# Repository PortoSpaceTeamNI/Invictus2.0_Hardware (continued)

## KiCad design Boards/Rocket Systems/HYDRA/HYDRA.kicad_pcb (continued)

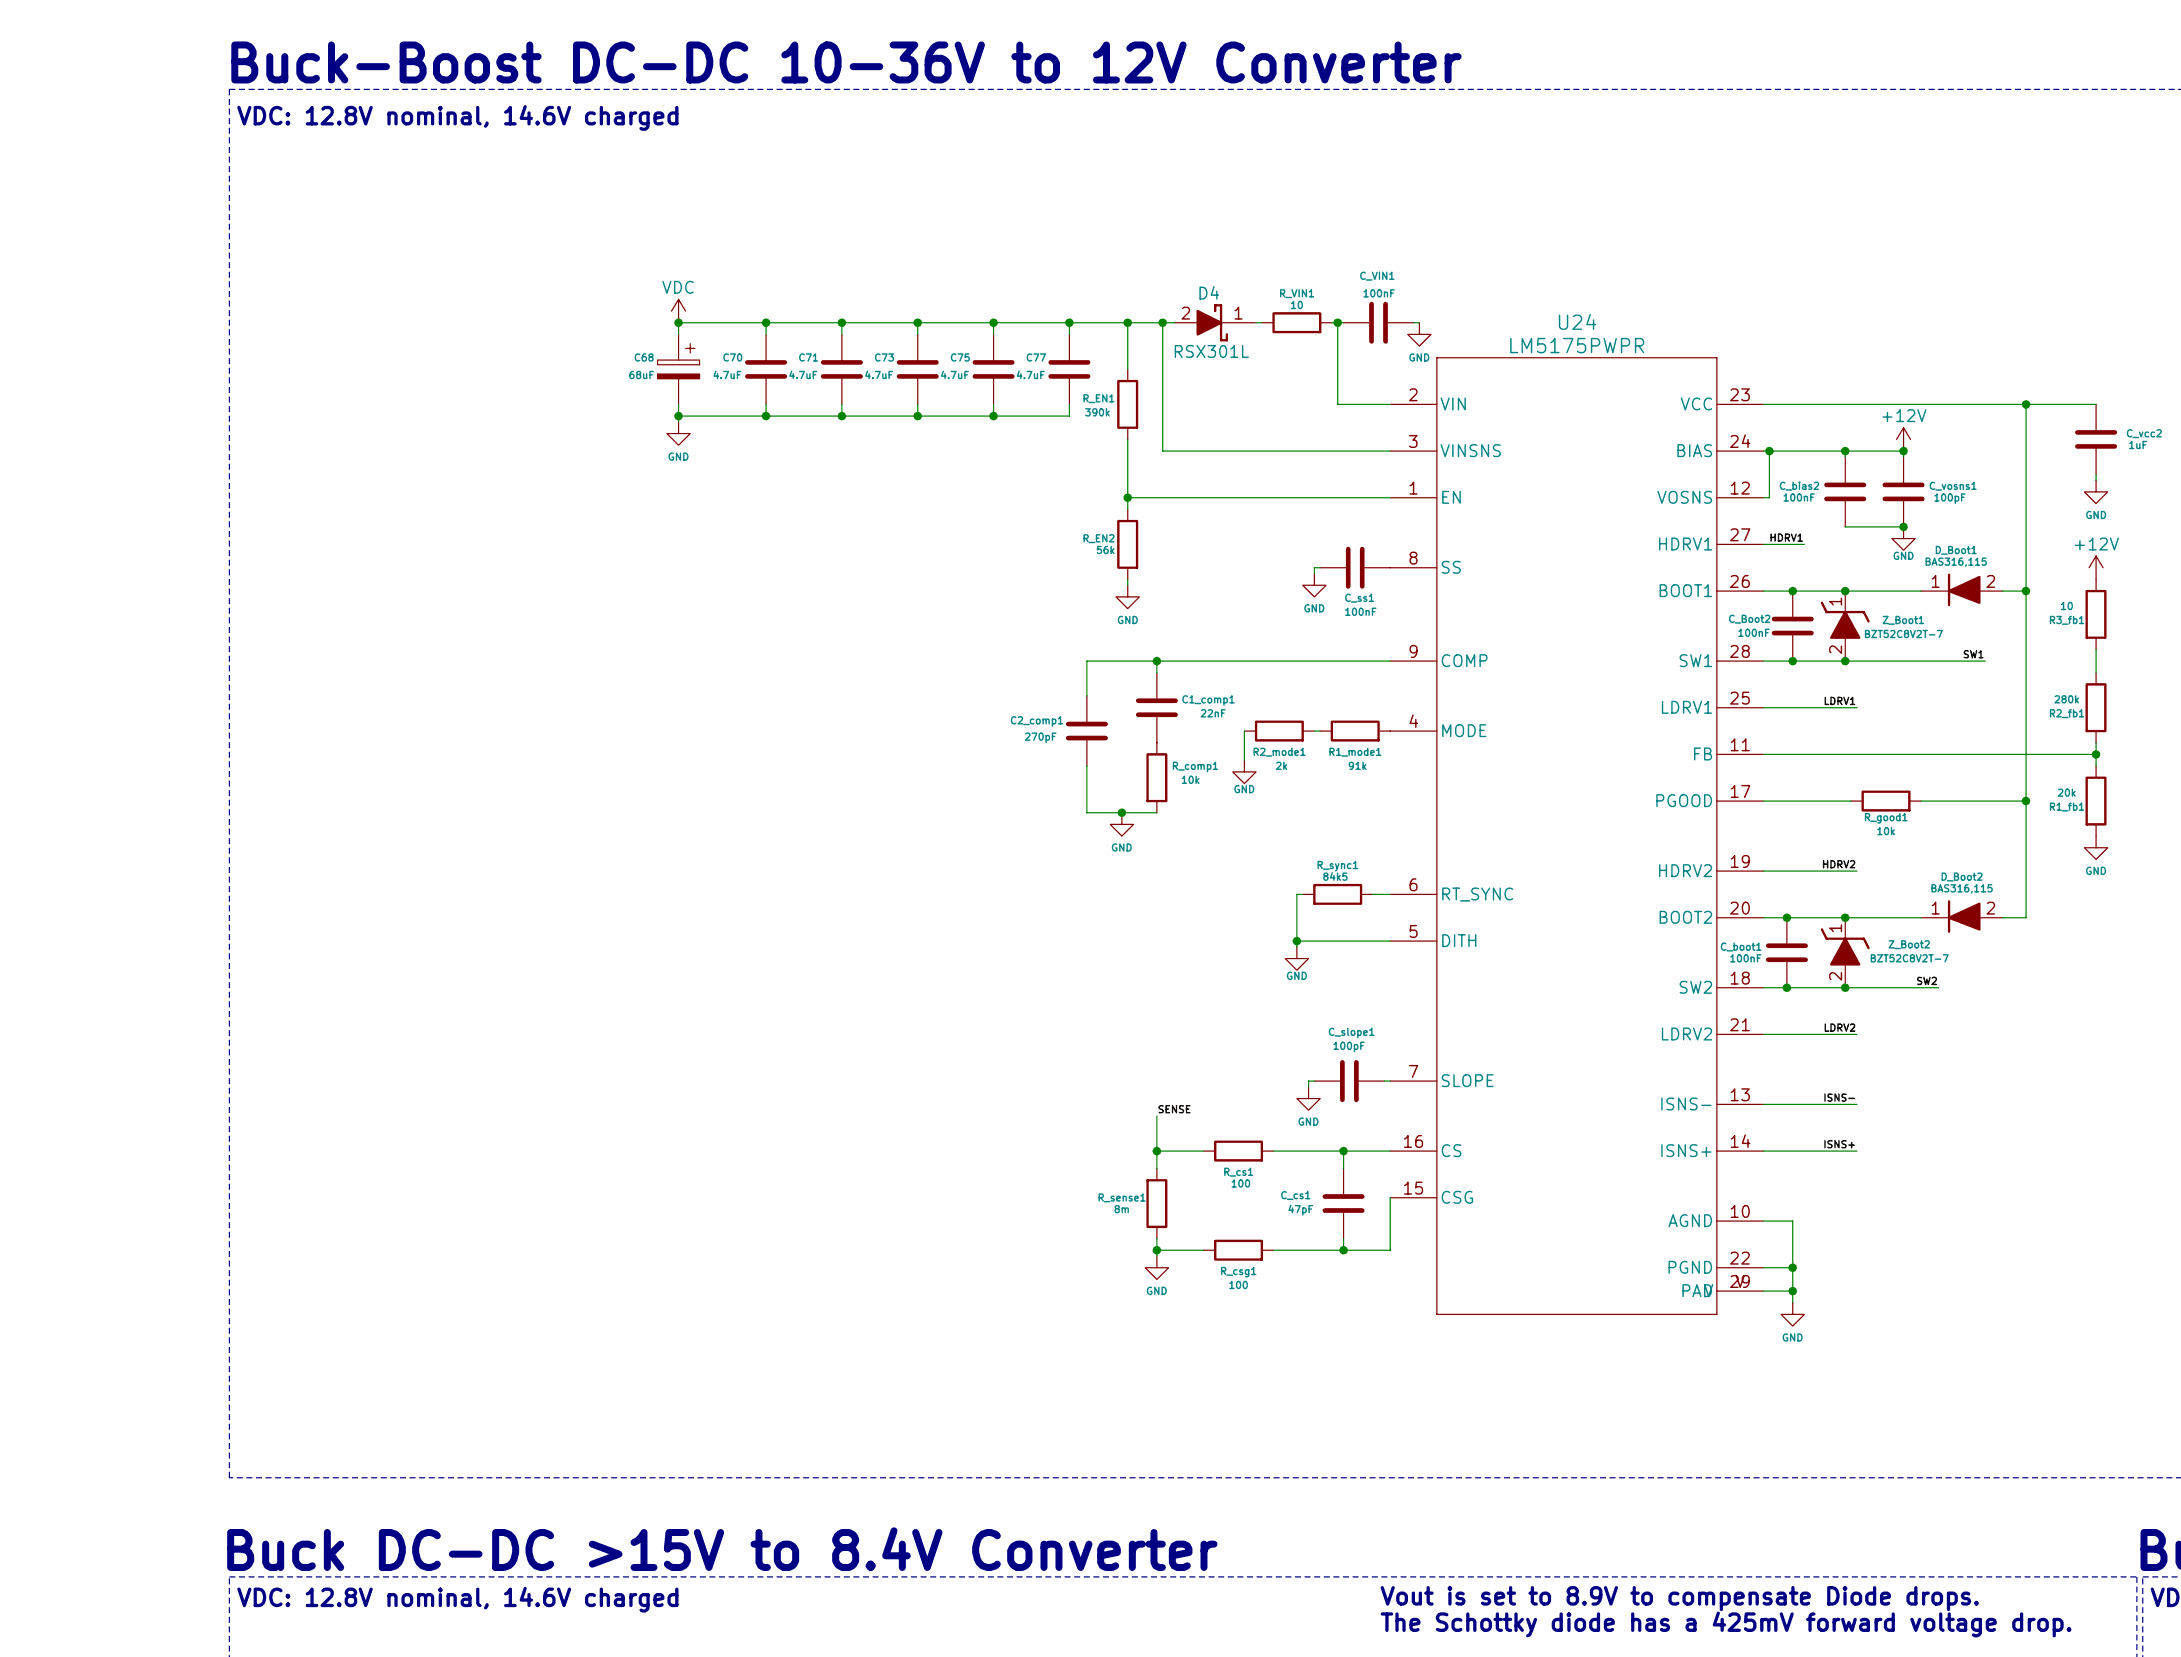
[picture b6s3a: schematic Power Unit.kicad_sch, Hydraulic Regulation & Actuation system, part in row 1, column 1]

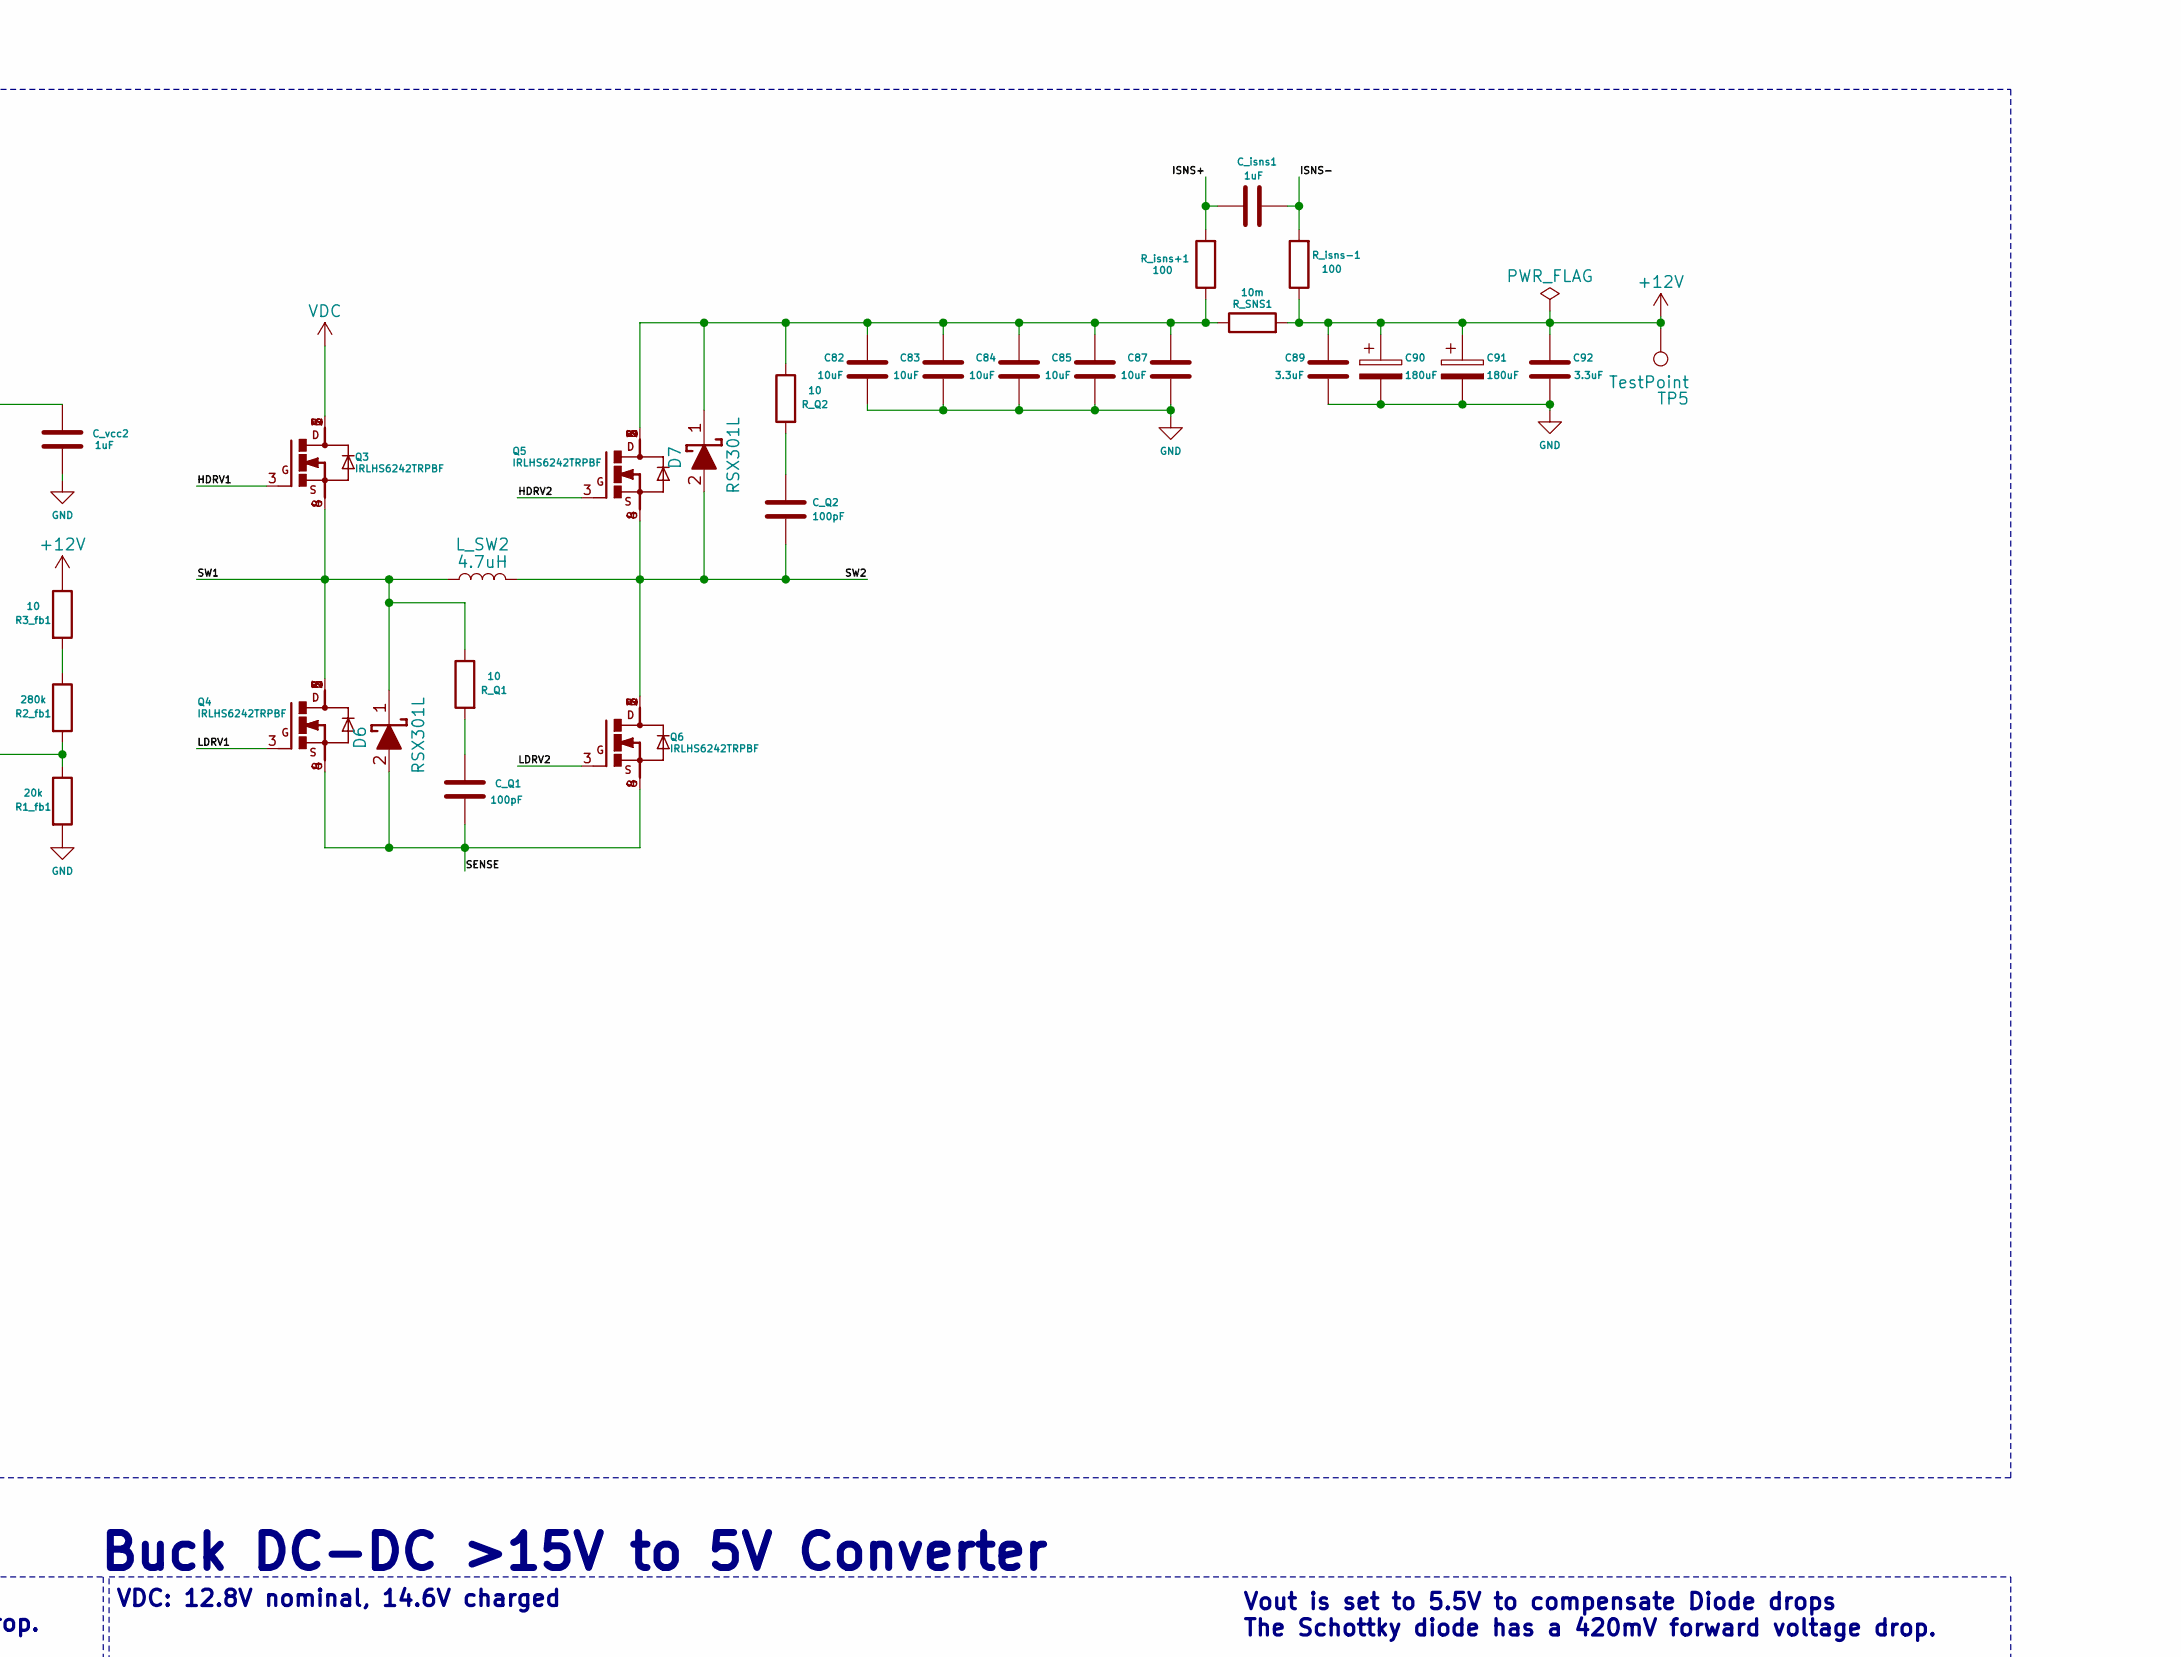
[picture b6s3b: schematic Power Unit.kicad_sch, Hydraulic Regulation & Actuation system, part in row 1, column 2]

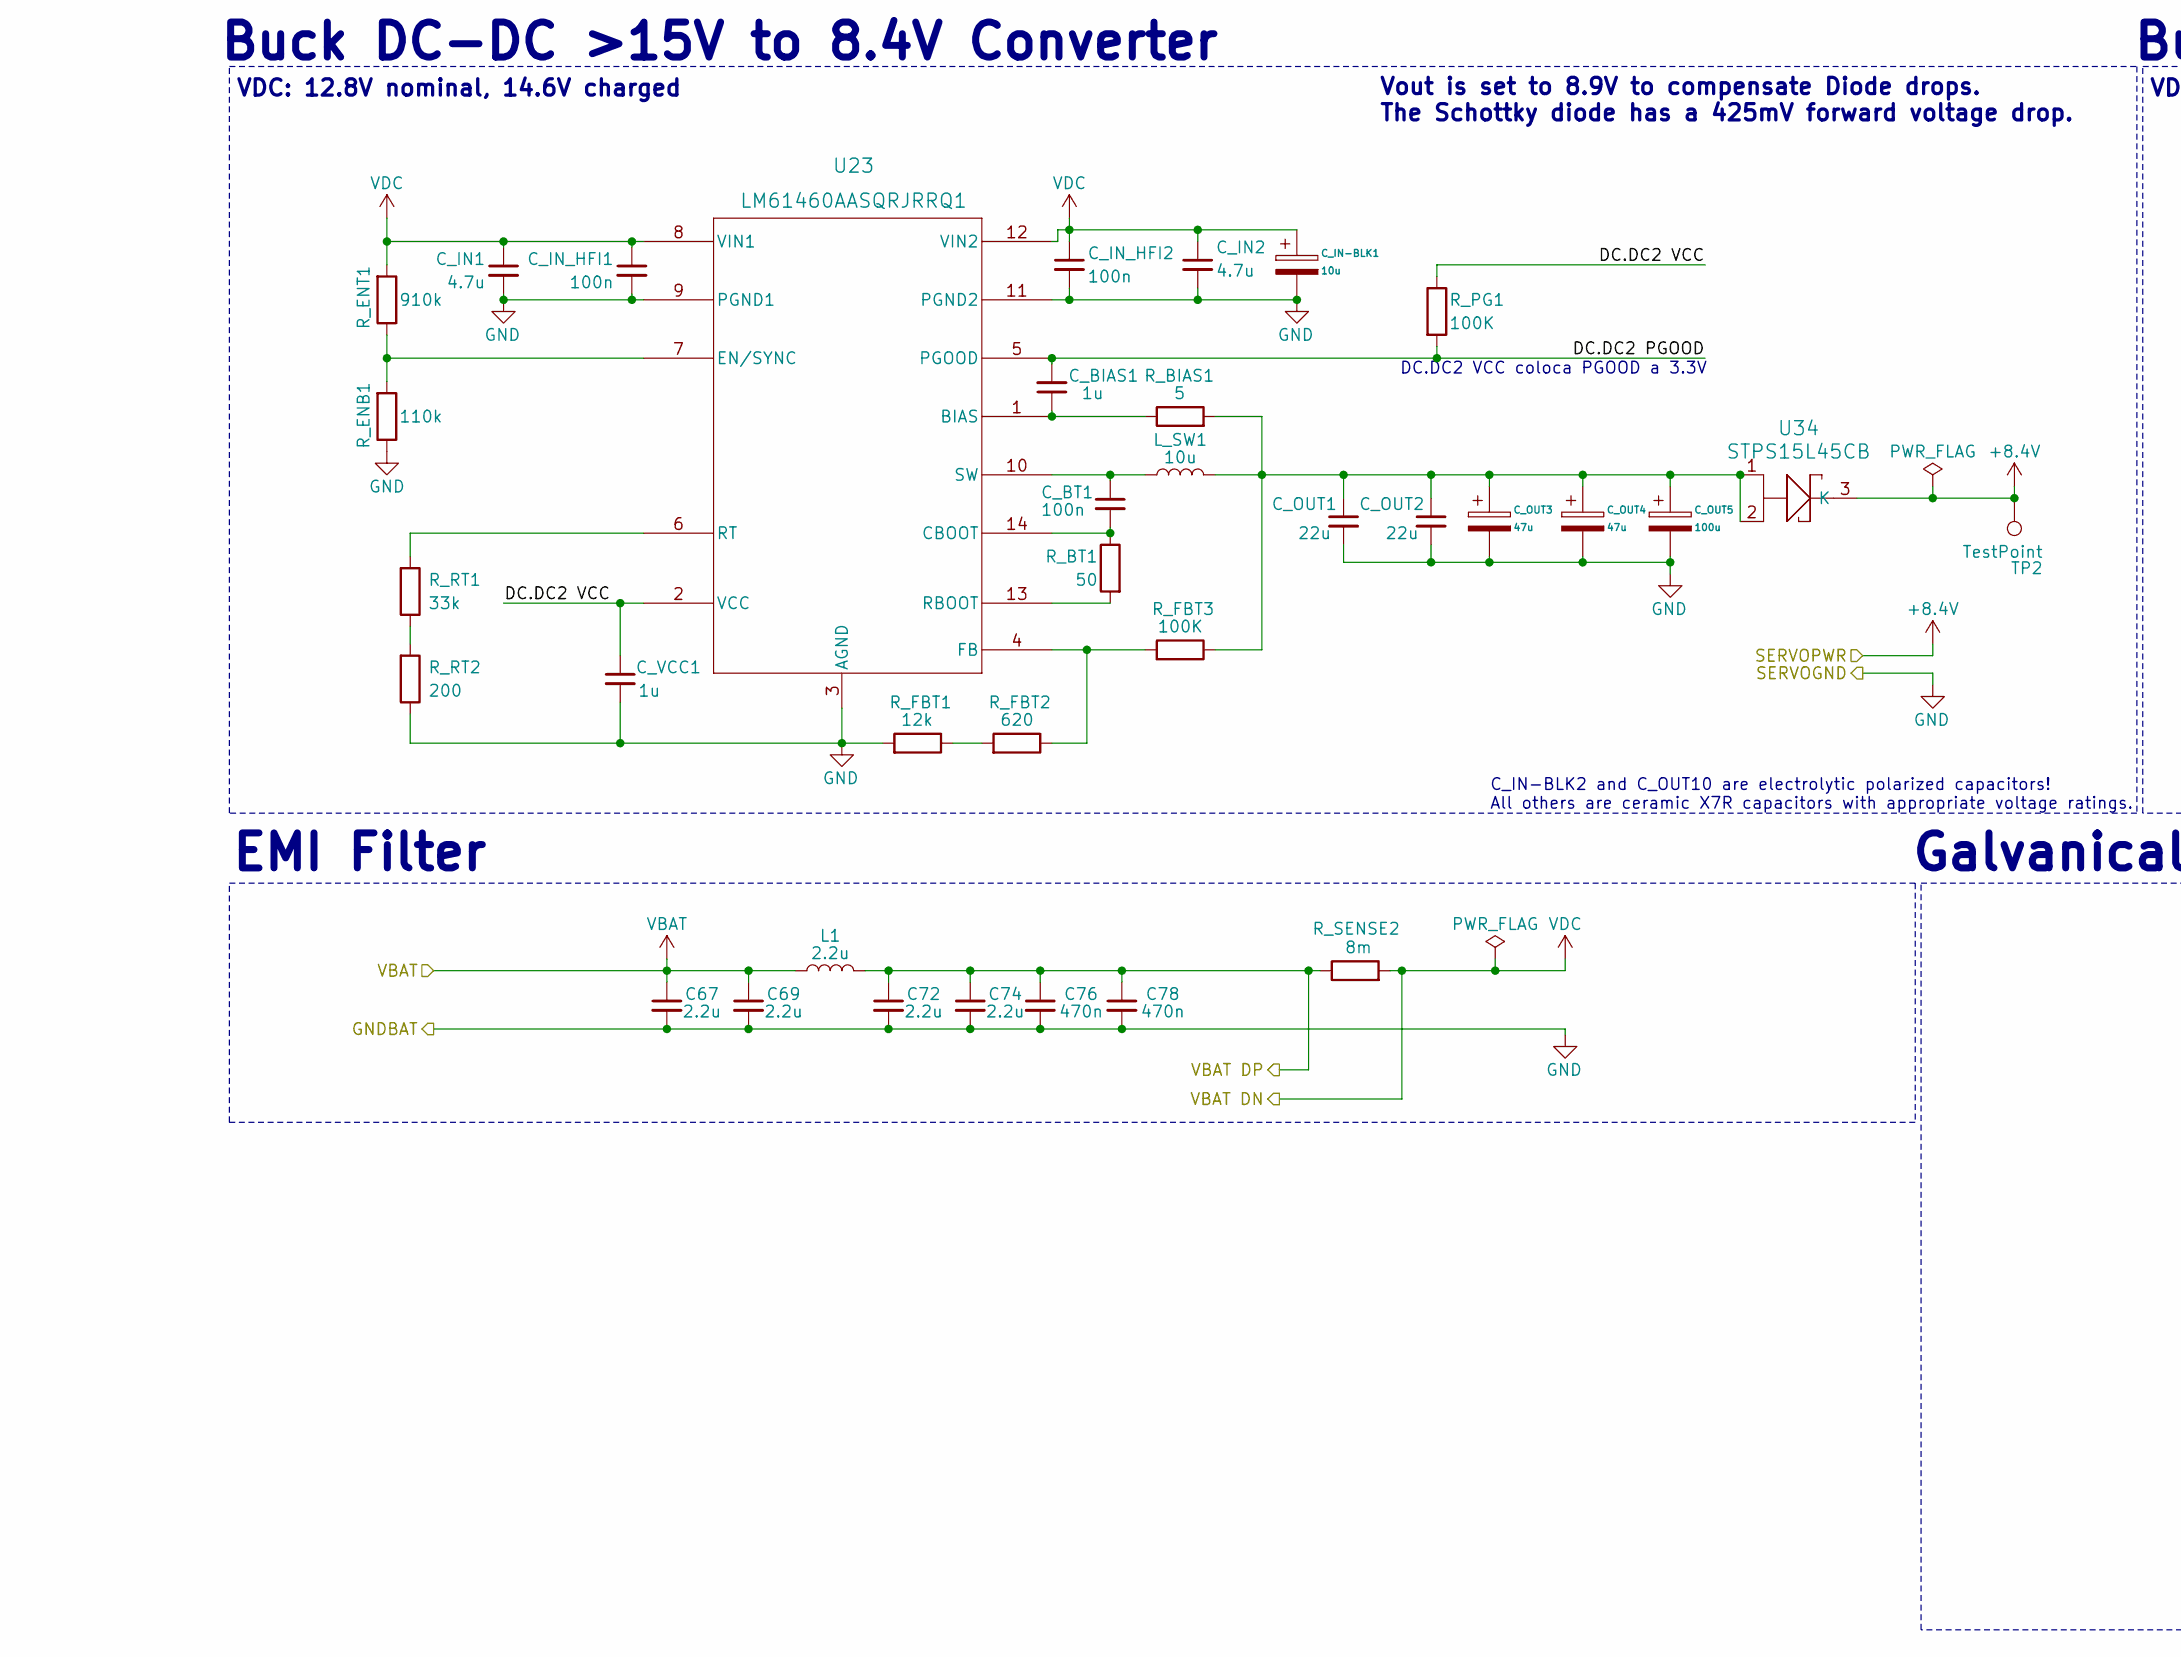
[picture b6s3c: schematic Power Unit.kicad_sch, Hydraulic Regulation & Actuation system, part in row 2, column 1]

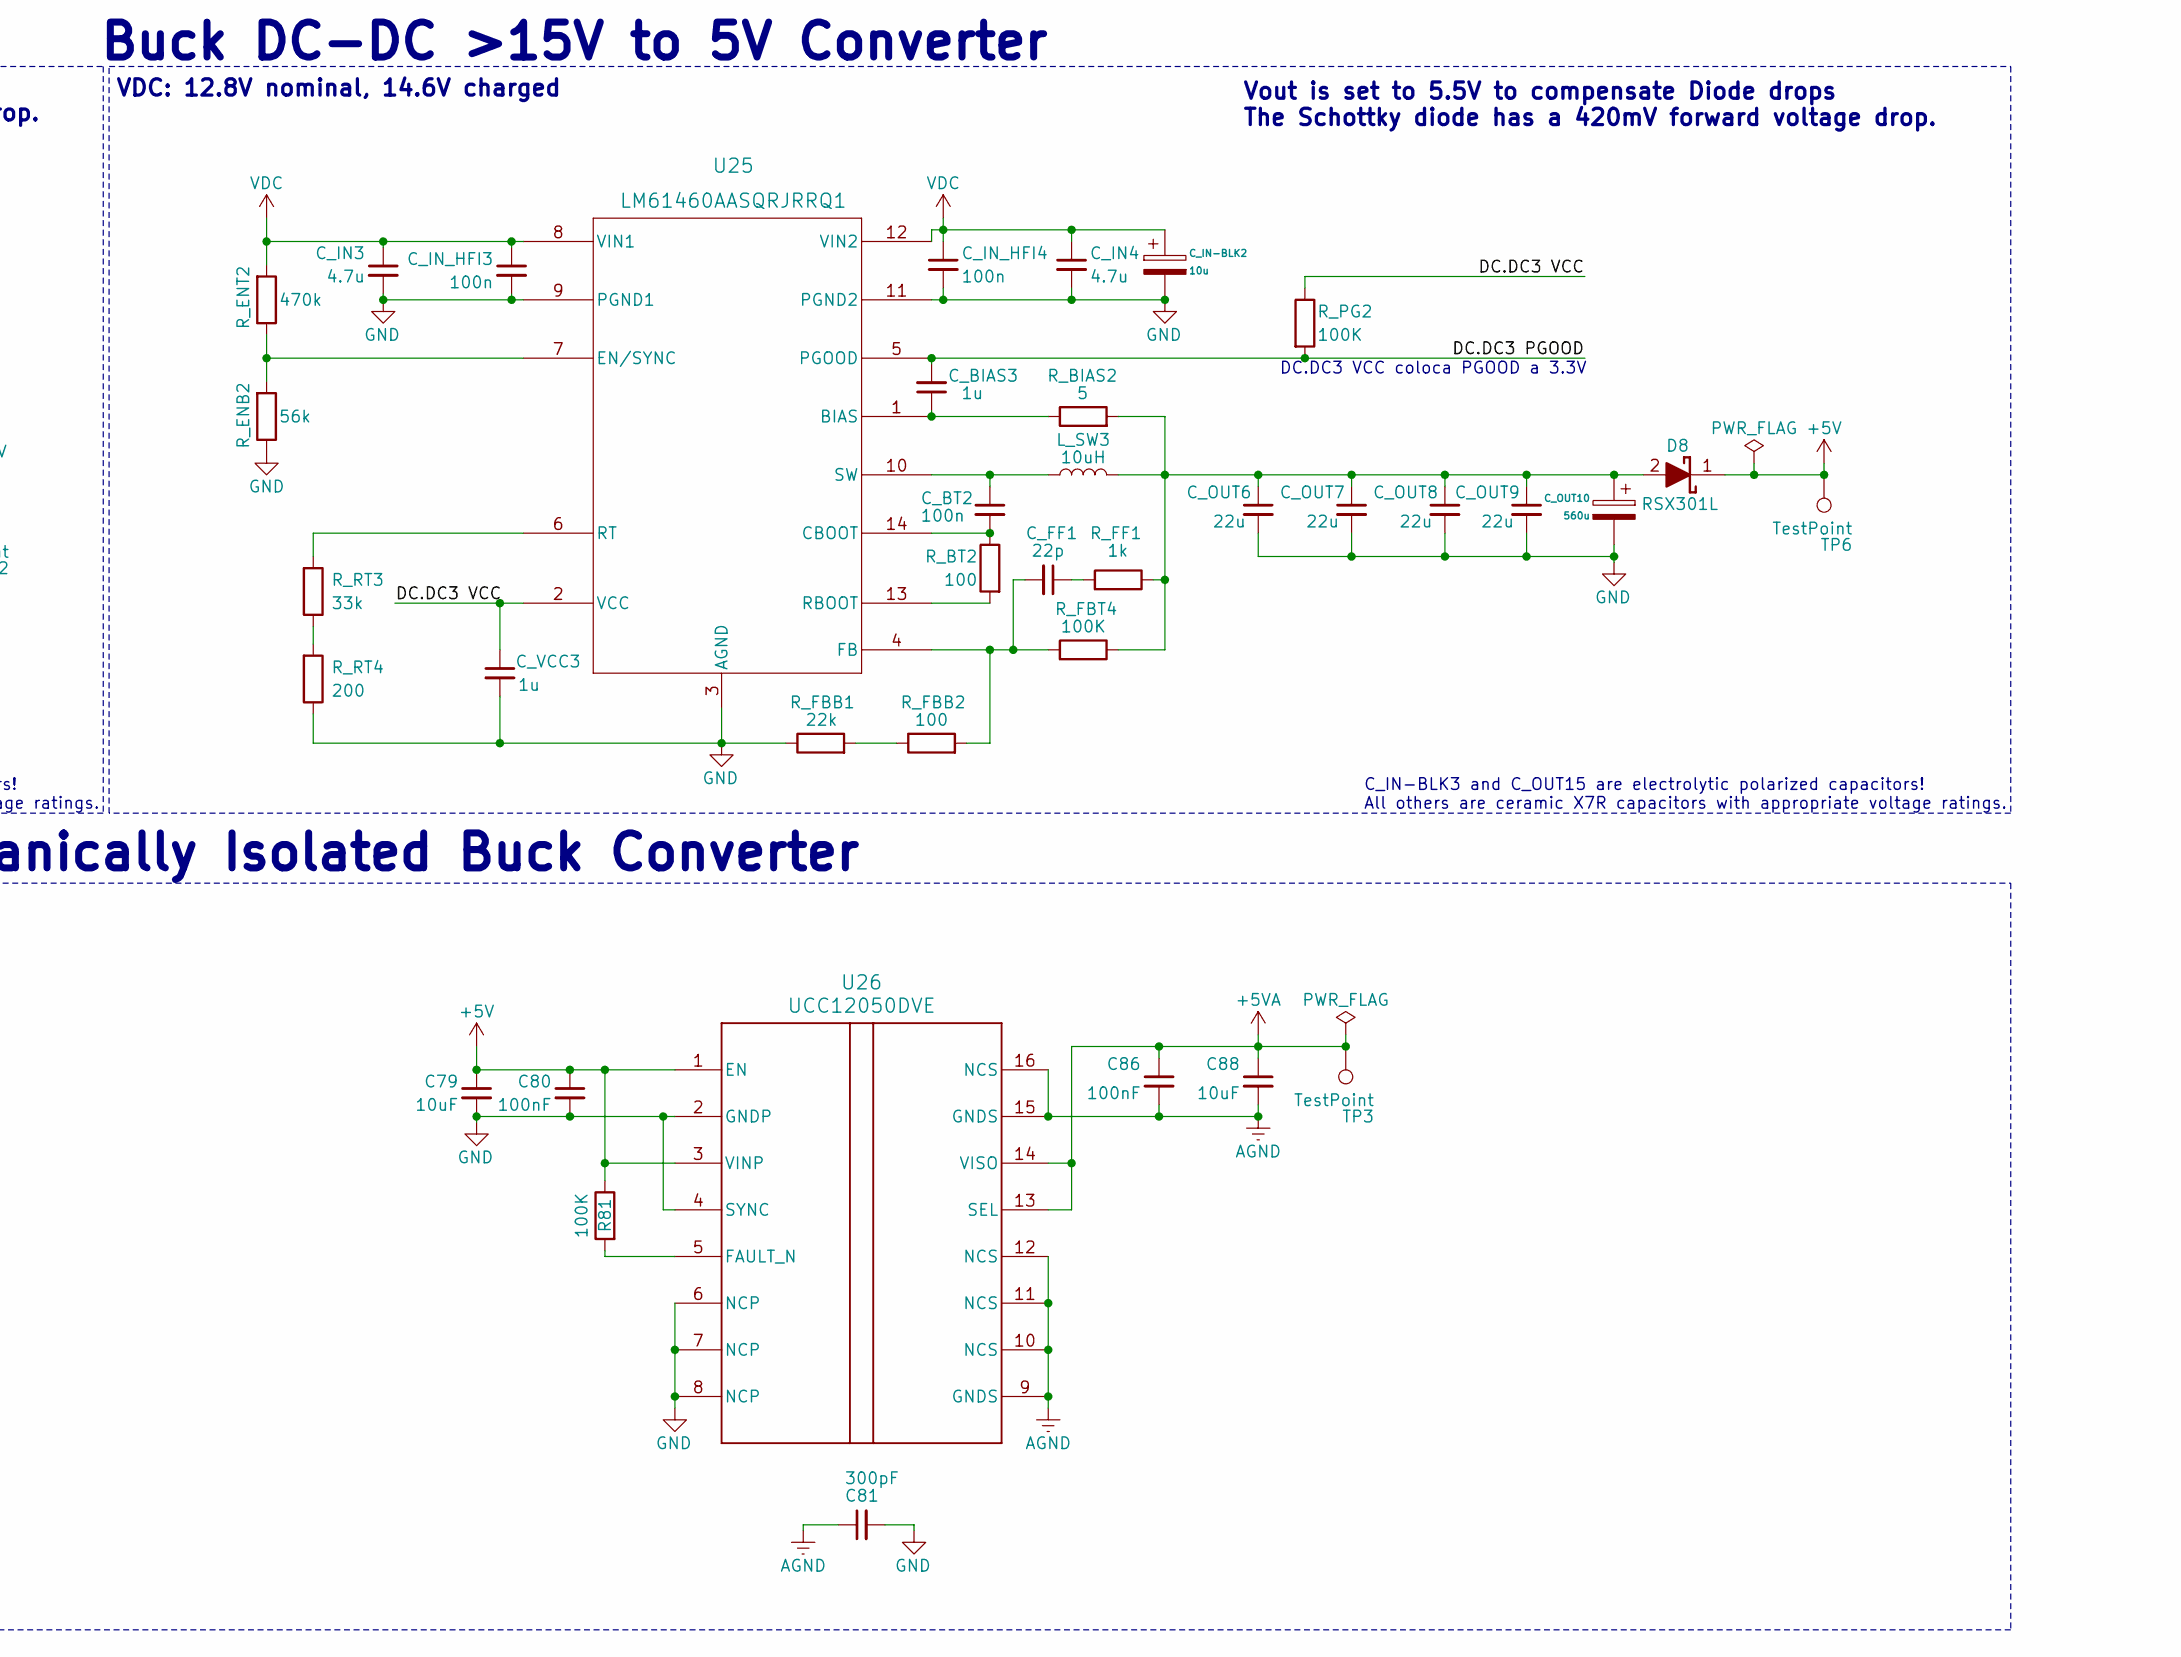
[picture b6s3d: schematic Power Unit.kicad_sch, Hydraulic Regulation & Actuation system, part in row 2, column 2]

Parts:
C1_comp1: 22nF; Capacitor_0603
C2_comp1: 270pF; Capacitor_0603
C67, C69, C72, C74: 2.2u; Capacitor_1206
C68: 68uF; CAP_WCAP-ATG8_6.3x11_WRE
C70, C71, C73, C75, C77: 4.7uF; Capacitor_1206
C76, C78: 470n; Capacitor_1206
C79, C88: 10uF; Capacitor_0805
C80, C86: 100nF; Capacitor_0603
C81: 300pF; C1808
C82, C83, C84, C85, C87: 10uF; Capacitor_1206
C89, C92: 3.3uF; Capacitor_0805
C90, C91: 180uF; CAP_WCAP-ATG8_8x11.5_WRE
C_BIAS1, C_BIAS3: 1u; Capacitor_0603
C_BT1, C_BT2: 100n; Capacitor_0402
C_Boot2: 100nF; Capacitor_0402
C_FF1: 22p; Capacitor_0402
C_IN1, C_IN2, C_IN3, C_IN4: 4.7u; Capacitor_1206
C_IN-BLK1, C_IN-BLK2: 10u; Capacitor_4mm
C_IN_HFI1, C_IN_HFI2, C_IN_HFI3, C_IN_HFI4: 100n; Capacitor_0603
C_OUT1, C_OUT2, C_OUT6, C_OUT7, C_OUT8, C_OUT9: 22u; Capacitor_0805
C_OUT3, C_OUT4: 47u; CAP_WCAP-ATG8_6.3x11_WRE
C_OUT5: 100u; Capacitor-6.3mm
C_OUT10: 560u; Capacitor_8mm
C_Q1, C_Q2: 100pF; Capacitor_0603
C_VCC1, C_VCC3: 1u; Capacitor_0603
C_VIN1: 100nF; Capacitor_0402
C_bias2: 100nF; Capacitor_0402
C_boot1: 100nF; Capacitor_0402
C_cs1: 47pF; Capacitor_0402
C_isns1: 1uF; Capacitor_0603
C_slope1: 100pF; Capacitor_0402
C_ss1: 100nF; Capacitor_0402
C_vcc2: 1uF; Capacitor_0603
C_vosns1: 100pF; Capacitor_0402
D4, D6, D7, D8: RSX301L; DIOM5026X220N; Mouser Part Number 755-RSX301L-30DDTE25
D_Boot1, D_Boot2: BAS316,115; BAS316115; Mouser Part Number 771-BAS316-T/R
L1: 2.2u; SRP6030CA-2R2M
L_SW1: 10u; Inductor-7.3mm-10u
L_SW2: 4.7uH; Inductor-7.2mm-4u7
L_SW3: 10uH; Inductor-7.3mm-10u
Q3, Q4, Q5, Q6: IRLHS6242TRPBF; QFN65P200X200X100-8N
R1_fb1: 20k; RES_0402
R1_mode1: 91k; RES_0402
R2_fb1: 280k; RES_0402
R2_mode1: 2k; RES_0402
R3_fb1: 10; RES_0402
R81: 100K; RES_0402
R_BIAS1, R_BIAS2: 5; RES_0402
R_BT1: 50; RES_0402
R_BT2: 100; RES_0402
R_EN1: 390k; RES_0402
R_EN2: 56k; RES_0402
R_ENB1: 110k; RES_0402
R_ENB2: 56k; RES_0402
R_ENT1: 910k; RES_0402
R_ENT2: 470k; RES_0402
R_FBB1: 22k; RES_0402
R_FBB2: 100; RES_0402
R_FBT1: 12k; RES_0402
R_FBT2: 620; RES_0402
R_FBT3, R_FBT4: 100K; RES_0402
R_FF1: 1k; RES_0402
R_PG1, R_PG2: 100K; RES_0402
R_Q1, R_Q2: 10; RES_1206
R_RT1, R_RT3: 33k; RES_0402
R_RT2, R_RT4: 200; RES_0402
R_SENSE2: 8m; RES_2512
R_SNS1: 10m; RES_1206
R_VIN1: 10; RES_0603
R_comp1: 10k; RES_0402
R_cs1: 100; RES_0402
R_csg1: 100; RES_0402
R_good1: 10k; RES_0402
R_isns+1: 100; RES_0402
R_isns-1: 100; RES_0402
R_sense1: 8m; RES_0805
R_sync1: 84k5; RES_0402
TP2, TP3, TP5, TP6: TestPoint; TestPoint_Pad_1.0x1.0mm
U23, U25: LM61460AASQRJRRQ1; VQFN-HR14_RJR_TEX
U24: LM5175PWPR; PWP0028F_L
U26: UCC12050DVE; DVE0016A
U34: STPS15L45CB; DPAK_STM
Z_Boot1, Z_Boot2: BZT52C8V2T-7; BZT52C8V2T7; Mouser Part Number 621-BZT52C8V2T-7

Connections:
+5V: C79.1, C80.1, D8.1 (K), R81.1, TP6.1, U26.1 (EN), U26.3 (VINP); also elsewhere on the board
+5VA: C86.1, C88.1, TP3.1, U26.13 (SEL), U26.14 (VISO); also elsewhere on the board
+8.4V: TP2.1, U34.3 (K); also elsewhere on the board
+12V: C89.2, C90.1, C91.1, C92.2, C_bias2.1, C_vosns1.1, R3_fb1.1, R_SNS1.2, R_isns-1.1, TP5.1, U24.12 (VOSNS), U24.24 (BIAS); also elsewhere on the board
/Power Unit/DC.DC2 PGOOD: C_BIAS1.2, R_PG1.2, U23.5 (PGOOD)
/Power Unit/DC.DC2 VCC: C_VCC1.1, R_PG1.1, U23.2 (VCC)
/Power Unit/DC.DC3 PGOOD: C_BIAS3.2, R_PG2.2, U25.5 (PGOOD)
/Power Unit/DC.DC3 VCC: C_VCC3.1, R_PG2.1, U25.2 (VCC)
/Power Unit/HDRV1: Q3.3, U24.27 (HDRV1)
/Power Unit/HDRV2: Q5.3, U24.19 (HDRV2)
/Power Unit/ISNS+: C_isns1.2, R_isns+1.2, U24.14 (ISNS+)
/Power Unit/ISNS-: C_isns1.1, R_isns-1.2, U24.13 (ISNS-)
/Power Unit/LDRV1: Q4.3, U24.25 (LDRV1)
/Power Unit/LDRV2: Q6.3, U24.21 (LDRV2)
/Power Unit/SENSE: C_Q1.2, D6.2 (A), Q4.4, Q4.8, Q6.4, Q6.8, R_cs1.1, R_sense1.2
/Power Unit/SW1: C_Boot2.2, D6.1 (K), L_SW2.1, Q3.4, Q3.8, Q4.1, Q4.2, Q4.5, Q4.6, Q4.7, R_Q1.1, U24.28 (SW1), Z_Boot1.2 (A)
/Power Unit/SW2: C_Q2.2, C_boot1.2, D7.2 (A), L_SW2.2, Q5.4, Q5.8, Q6.1, Q6.2, Q6.5, Q6.6, Q6.7, U24.18 (SW2), Z_Boot2.2 (A)
/Power Unit/VBAT DP: C72.1, C74.1, C76.1, C78.1, L1.2, R_SENSE2.1; also elsewhere on the board
AGND: C81.1, C86.2, C88.2, U26.9 (GNDS), U26.10 (NCS), U26.11 (NCS), U26.12 (NCS), U26.15 (GNDS), U26.16 (NCS); also elsewhere on the board
GND: C2_comp1.1, C67.2, C68.2, C69.2, C70.1, C71.1, C72.2, C73.1, C74.2, C75.1, C76.2, C77.1, C78.2, C79.2, C80.2, C81.2, C82.1, C83.1, C84.1, C85.1, C87.1, C89.1, C90.2, C91.2, C92.1, C_IN1.2, C_IN2.2, C_IN3.2, C_IN4.2, C_IN-BLK1.2, C_IN-BLK2.2, C_IN_HFI1.2, C_IN_HFI2.2, C_IN_HFI3.2, C_IN_HFI4.2, C_OUT1.2, C_OUT2.2, C_OUT3.2, C_OUT4.2, C_OUT5.2, C_OUT6.2, C_OUT7.2, C_OUT8.2, C_OUT9.2, C_OUT10.2, C_VCC1.2, C_VCC3.2, C_VIN1.2, C_bias2.2, C_slope1.2, C_ss1.2, C_vcc2.2, C_vosns1.2, R1_fb1.2, R2_mode1.1, R_EN2.2, R_ENB1.1, R_ENB2.1, R_FBB1.1, R_FBT1.2, R_RT2.1, R_RT4.1, R_comp1.2, R_csg1.1, R_sense1.1, R_sync1.2, U23.3 (AGND), U23.9 (PGND1), U23.11 (PGND2), U24.5 (DITH), U24.10 (AGND), U24.22 (PGND), U24.29 (PAD), U24.V, U25.3 (AGND), U25.9 (PGND1), U25.11 (PGND2), U26.2 (GNDP), U26.4 (SYNC), U26.6 (NCP), U26.7 (NCP), U26.8 (NCP); also elsewhere on the board
unnamed: C1_comp1.1, R_comp1.1
unnamed: C_FF1.1, R_FF1.2
unnamed: C_OUT1.1, C_OUT2.1, C_OUT3.1, C_OUT4.1, C_OUT5.1, L_SW1.2, R_BIAS1.2, R_FBT3.1, U34.1, U34.2
unnamed: C_Q1.1, R_Q1.2
unnamed: C_Q2.1, R_Q2.2
unnamed: D4.1 (K), R_VIN1.1
unnamed: C82.2, C83.2, C84.2, C85.2, C87.2, D7.1 (K), Q5.1, Q5.2, Q5.5, Q5.6, Q5.7, R_Q2.1, R_SNS1.1, R_isns+1.1
unnamed: C_OUT6.1, C_OUT7.1, C_OUT8.1, C_OUT9.1, C_OUT10.1, D8.2 (A), L_SW3.2, R_BIAS2.2, R_FBT4.1, R_FF1.1
unnamed: C_vcc2.1, D_Boot1.2 (A), D_Boot2.2 (A), R_good1.2, U24.23 (VCC)
unnamed: C_Boot2.1, D_Boot1.1 (K), U24.26 (BOOT1), Z_Boot1.1 (K)
unnamed: C_boot1.1, D_Boot2.1 (K), U24.20 (BOOT2), Z_Boot2.1 (K)
unnamed: R1_mode1.1, R2_mode1.2
unnamed: R2_fb1.1, R3_fb1.2
unnamed: R_FBB1.2, R_FBB2.1
unnamed: R_FBT1.1, R_FBT2.2
unnamed: R_RT1.1, R_RT2.2
unnamed: R_RT3.1, R_RT4.2
unnamed: C_BIAS1.1, R_BIAS1.1, U23.1 (BIAS)
unnamed: C_BT1.2, R_BT1.1, U23.14 (CBOOT)
unnamed: R_ENB1.2, R_ENT1.1, U23.7 (EN/SYNC)
unnamed: R_FBT2.1, R_FBT3.2, U23.4 (FB)
unnamed: R_BT1.2, U23.13 (RBOOT)
unnamed: R_RT1.2, U23.6 (RT)
unnamed: C_BT1.1, L_SW1.1, U23.10 (SW)
unnamed: C1_comp1.2, C2_comp1.2, U24.9 (COMP)
unnamed: C_cs1.2, R_cs1.2, U24.16 (CS)
unnamed: C_cs1.1, R_csg1.2, U24.15 (CSG)
unnamed: R_EN1.2, R_EN2.1, U24.1 (EN)
unnamed: R1_fb1.1, R2_fb1.2, U24.11 (FB)
unnamed: R1_mode1.2, U24.4 (MODE)
unnamed: R_good1.1, U24.17 (PGOOD)
unnamed: R_sync1.1, U24.6 (RT_SYNC)
unnamed: C_slope1.1, U24.7 (SLOPE)
unnamed: C_ss1.1, U24.8 (SS)
unnamed: C_VIN1.1, R_VIN1.2, U24.2 (VIN)
unnamed: C_BIAS3.1, R_BIAS2.1, U25.1 (BIAS)
unnamed: C_BT2.2, R_BT2.1, U25.14 (CBOOT)
unnamed: R_ENB2.2, R_ENT2.1, U25.7 (EN/SYNC)
unnamed: C_FF1.2, R_FBB2.2, R_FBT4.2, U25.4 (FB)
unnamed: R_BT2.2, U25.13 (RBOOT)
unnamed: R_RT3.2, U25.6 (RT)
unnamed: C_BT2.1, L_SW3.1, U25.10 (SW)
unnamed: R81.2, U26.5 (FAULT_N)
VBAT: C67.1, C69.1, L1.1; also elsewhere on the board
VDC: C68.1, C70.2, C71.2, C73.2, C75.2, C77.2, C_IN1.1, C_IN2.1, C_IN3.1, C_IN4.1, C_IN-BLK1.1, C_IN-BLK2.1, C_IN_HFI1.1, C_IN_HFI2.1, C_IN_HFI3.1, C_IN_HFI4.1, D4.2 (A), Q3.1, Q3.2, Q3.5, Q3.6, Q3.7, R_EN1.1, R_ENT1.2, R_ENT2.2, R_SENSE2.2, U23.8 (VIN1), U23.12 (VIN2), U24.3 (VINSNS), U25.8 (VIN1), U25.12 (VIN2); also elsewhere on the board

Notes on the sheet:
Buck-Boost DC-DC 10-36V to 12V Converter
C_IN-BLK3 and C_OUT15 are electrolytic polarized capacitors! All others are ceramic X7R capacitors with appropriate voltage ratings.
DC.DC3 VCC coloca PGOOD a 3.3V
Vout is set to 5.5V to compensate Diode drops The Schottky diode has a 420mV forward voltage drop.
Buck DC-DC >15V to 8.4V Converter
Vout is set to 8.9V to compensate Diode drops. The Schottky diode has a 425mV forward voltage drop.
VDC: 12.8V nominal, 14.6V charged
DC.DC2 VCC coloca PGOOD a 3.3V
Buck DC-DC >15V to 5V Converter
C_IN-BLK2 and C_OUT10 are electrolytic polarized capacitors! All others are ceramic X7R capacitors with appropriate voltage ratings.
EMI Filter
Galvanically Isolated Buck Converter
